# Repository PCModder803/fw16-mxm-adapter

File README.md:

# FW16 Expansion Bay -> MXM adapter : schematic v4 (full mock-up, with placeholders)

Open `fw16_mxm_adapter.kicad_pro` in KiCad (built and checked with KiCad 10). The project
footprint library `fw16_mxm.pretty` is registered through `fp-lib-table`.
`fw16_mxm_adapter_schematic.pdf` shows the same schematic (one A0 sheet) with no KiCad needed.
`fw16_mxm_adapter_bom_draft.csv` lists every part with its footprint and notes; "TBD" marks an unresolved choice.

Target: Graphics Module bay, MXM 3.0 Type B card (X-Vision RX 6600 XT): 100 W total board power
(105 W TDP), 82 x 105 mm, 0-55 C operating, supplied bare with no cooler. At 100 W it draws 5.0 A from
VSYS at 20 V (AC) or 6.6 A at 15.2 V (battery), within the eFuse's 9.9 A limit and the host's 10.5 A.

Third-party documents (Framework's PDFs and drawings, datasheets, and the crops in `reference/evidence/`)
are kept locally but not published in this repository; the tables below name each source.
The community board this started from is on the Framework forum (t/74018).

## What is in the schematic
| Block | Parts | Source |
|---|---|---|
| Signal interposer | J1, 74 pins | FrameworkComputer/ExpansionBay Electrical/README.md |
| Power interposer | J2, 74 pins | same |
| MXM 3.0 socket | J3, 278 pins (Foxconn AS0B826-S55B-7H) | MXM 3.1 r1.0 Table 3.2/3.3 (all 278 pins checked); ADLINK MXM-AXe + Advantech SKY-MXM-RTX3000 manuals |
| MXM system-board parts | U6 SN74LV1T08 (card PWR_EN = 1.8 V host PWR_EN AND eFuse PG, at 3.3 V; R19 100k pull-down, R40 PG pull-up, C48); R36 PEX_STD_SW# 7.15k pull-down; R37 PWR_GOOD and R38 TH_ALERT# 10k pull-ups | MXM 3.1 sec 3.4.1, Tables 3.6, 3.11, 3.30 |
| PCIe x8 | R20-R35 0R (host->card), C10-C25 220 nF (card->host) | community board + a-little-wifi frmw-16-MXM-E-port |
| DisplayPort A (internal panel) | C26-C35 100 nF DC blocking; HPD direct, R14 DNP | Advantech manual: DC blocking + HPD conditioning on the system board |
| Card power | D1 SMBJ20A; U1 TPS25982 eFuse: ILIM 147R = 9.9 A, UVLO 6.5 V (442k/100k), IMON 1.33k, dVdT 4.7 nF (~1 V/ms), retry 2.2 nF (~100 ms, 4 retries then latch-off); C1/C4 EEH-ZA1V101P | TI datasheet SLVSEI3D equations; SMBJ20A / EEH-ZA1V101P distributor data |
| 5 V / 3.3 V | host 5V_ALW (2.5 A) / 3V3_ALW (2.0 A), C2/C3 bulk | ExpansionBay README |
| Power control | host PWR_EN (1.8 V APU GPIO) -> U6 -> MXM PWR_EN; MXM PWR_GOOD -> host PWR_GOOD and pin 53 | MXM 3.1 sec 3.4.1; 1.8 V level from Framework forum t/74018 post 233; U6 per TI SCLS739F |
| PEX_RST# source | R41 0R (fitted): host PEX_RST#. R42 0R DNP: power pin 52 (EC's EXT_SSD1_RST# in SSD-mode descriptors). Fit one only | Fallback for the BIOS dropping PEX_RST# with x8 descriptors (forum t/74018 posts 201-203) |
| Thermal / panel | TH_OVERT#, TH_ALERT#, PNL_* straight J1 <-> J3 | community board, a-little-wifi |
| Module EEPROM | U3 BR24G32 (32 Kbit) at 0x50 on I2C_*_ALW | FW EC gpu_configuration.c reads 0x50 with 16-bit offsets |
| Module ID | R1/R2 330k on ID0/ID1 -> BOARD_VERSION_12 on both = "dual interposer device" | FW EC gpu.c + adc.c thresholds; forum t/74018 original poster: 330k always passed detection |
| Power pins 52/53 | R13 0R: PWR_GOOD -> pin 53 (FBVDD_PWRGD in GPU mode); pin 52 (GC6_FB_EN3V3) NC; MXM SMB_CLK/DAT NC | FW16 7040 mainboard interface schematic p.3 (UC77 / UC78) |
| Fans (graphics bay) | J4/J5 Hefeng AFC58-S04FIA-R1: 1 +12V, 2 SPEED, 3 PWM, 4 GND | FW_EXPANSION_BAY_PCB sheet 2 pin table; Hefeng AFC58 drawing; Cooler Master UMA fan spec (FPC 1 = -, 4 = +, mirrored) |
| Fan-control sensor | U4 F75303M (MSOP-10) @0x4D on I2C_*_ALW, remote diodes Q1/Q2 (MMBT3906) on the card's VRM / VRAM, C46/C47 2.2 nF across D+/D- | Framework PCIE_THERMAL_3RDPARTY descriptor; pinout, filter caps and address 0x4D (8-bit 0x9A) from the FW16 mainboard's own F75303M (7040 interface schematic p.9) |

## Footprints
- Stock KiCad footprints for passives, D1 (D_SMB), U3 (TSSOP-8) and U4 (MSOP-10_3x3mm_P0.5mm).
- U4 F75303M pinout: 1 VCC, 2 DP1, 3 DN1, 4 DP2, 5 DN2, 6 GND, 7 THERM#, 8 ALERT#, 9 SDA, 10 SCL, read
  from the FW16 mainboard's own sensor UTH1 (7040 interface schematic p.9).
- `TI_RGE0024M_VQFN-24_4x4mm_P0.5mm_2EP` (U1): TI example board layout 4223975/B. Pads 0.575 x 0.24 at
  0.5 mm, rows at 3.825 mm; pad 25 (IN) 2.7 x 1.45 at y -0.625, pad 26 (GND) 2.7 x 0.85 at y +0.925.
  Paste is not windowed yet; use TI's stencil drawing.
- `Hefeng_AFC58-S04F_1x04_P0.5mm_Horizontal` (J4/J5): Hefeng drawing. Pads 0.30 x 1.10 at 0.5 mm; nail pads
  1.0 x 2.0, inner edge 1.60 from pin 1, top edge 1.60 below the signal pads (read off the drawing; check it).
- Crops of the source drawings for both, and for the fan pinout, are kept locally in `reference/evidence/`
  (not published here).
- The interposer and MXM footprints in `fw16_mxm.pretty` were built from the community board in `reference/`:
  - `FW16_FXBeam_Signal` / `FW16_FXBeam_Power`: the community interposer footprint split in two, with pads
    renumbered by position to the Framework README pin numbers. This also removes the duplicate PJ1/PJ2/PJ3
    pad bug. Both footprints keep the original origin, so **J1 and J2 must be placed at the same XY**.
    The pad geometry is unverified against the FXBeam drawing.
  - `MXM3_AS0B826-S55B-7H`: the merged power pads are split so every MXM pin has a pad.
    S55B is chosen: 5.5 mm overall with a 2.7 mm gap under the card (Critical Link wiki; Foxconn's sheet
    gives only the overall height). The adapter PCB is 1.2 mm, matching Framework's reference board and its
    M2 inserts. Checked against Foxconn's AS-series datasheet: all pad positions match; pegs set to its
    1.10 / 1.60 mm; courtyard added.
  - The 2.7 mm interposer screw holes are 16.65 mm apart, matching Framework's FW_EXPANSION_BAY_PCB_0807
    drawing (`reference/framework_pcb_ref/`). They still need a solder ring for the ES00000NY00 insert.
- Every symbol pin has a matching footprint pad (checked from the netlist); all 88 parts have footprints.

## How the FW16 EC handles the bay (from FrameworkComputer/EmbeddedController, lotus sources)
- The EC reads ID0/ID1 on its ADC. BOARD_VERSION_12 on both is "dual interposer device". The bay only
  powers up while the F_BEAM hatch switch is closed.
- It then turns on the module's 3V/5V and waits 150 ms. Next it reads the EEPROM at 0x50 (fallback 0x52)
  with 16-bit offsets on I2C_PORT_GPU0, the ALW bus.
- **VSYS and the fans are enabled only by the EEPROM descriptor.** A blank EEPROM makes the EC fall back
  to dual-SSD mode (PCIe x4x2) with no GPU power.
- Program the descriptor from ExpansionBayConfigurationGenerator `PCIE_THERMAL_3RDPARTY`. That gives
  PCIE_8X1, VSYS_EN, FAN_EN, 3V_5V_EN and an F75303 at 0x4D for fan control. Two changes:
  - `GPU_PCIE_MUX_SEL` to LOW: the template sets it HIGH, which reroutes DP_A AUX to the SSD2 PCIe clock.
  - `gpio2` (GPU_2A2_GPIO2_EC) to `GPIO_FUNC_ACDC`, `GPIO_OUTPUT_LOW`, `POWER_S3`, as in Framework's r23m
    descriptor. The EC then drives it with `extpower_is_present()` (high on any external power), which
    sets the card's PWR_LEVEL through U2. Left as the template's input, the card stays at reduced power.
- The EC sets `GPU_PRESENT`, which the internal-panel eDP mux path uses, only for vendor `GPU_AMD_R23M`.
  Driving the laptop's own screen from the MXM card may need firmware changes.
- Power pins 52/53 are `GPU_1F3_MUX1` / `GPU_1G3_MUX2` in the EC ("cannot be controlled directly"):
  they go through mainboard switch UC77. With GPU_PCIE_MUX_SEL low they carry GC6_FB_EN3V3 (out) and
  FBVDD_PWRGD (in), and the mainboard ANDs FBVDD_PWRGD with DGPU_PWROK into ALL_GPWRGD (7040 interface
  schematic p.3). The adapter drives pin 53 from PWR_GOOD through R13.
- On Framework's own AMD module, GPIO0_EC is the temperature-fault input, GPIO1_EC is HPD from its PD
  controller, and GPIO2_EC is the AC/DC-mode output. GPIO3_EC is unused.

## Placeholders still in the design (TBD)
- U4 F75303M ALERT#/THERM# are open-drain and left unconnected; they need pull-ups only if something
  reads them.
- R14 (DNP): not needed. MXM 3.1 puts the 100k DP_A_HPD pull-down on the module.
- Unconnected by choice: TH_PWM, GPIO0/1/3_EC, DGPU_PWM_SEL, WAKE#, MXM SMB_CLK/DAT, power pins 52/54.
- Cover: the stock cover is too low over the card. It needs a 3D-printed replacement whose inside is flat
  at the 15.3 mm level. With S55B on 1.2 mm that leaves ~5 mm over the inductors and ~8.4 mm over the die
  for the cooler. See `RESEARCH_TODO.md` item 6.
- PWR_LEVEL: U2 (74LVC1G07) pulls the card's PWR_LEVEL low whenever GPIO2_EC is low, i.e. on battery.
  The card must then cut power by at least 20% (MXM 3.1 sec 3.4.14); how much the X-Vision VBIOS actually
  cuts is unknown. Leave U2 unfitted for always-full power.

## What was verified (kicad-cli 10)
- ERC: only "symbol library not in library table" warnings, for the symbols embedded by the generator.
  Connector pins are typed passive, so ERC can't catch direction mistakes.
- Netlist: every PCIe/DP lane, sideband net, power rail, eFuse pin and fan net was checked against the
  intended pins.
- Not verified: the schematic drawing's layout in detail (the PDF has only been looked over as a whole),
  and anything electrical or physical on hardware.

## Evidence for the PCIe direction
MXM lane names are system-relative: host PEX_TX -> MXM PEX_TX, MXM PEX_RX -> host PEX_RX.
Sources: a-little-wifi's frmw-16-MXM-E-port and mxm-immobilizer, the community board, and XPModder's IO
module for the Framework side. Confirmed by MXM 3.1 Table 3.6, and on the Framework side by the 7040
interface schematic: host->module lanes are PEG_CTX_C_GRX_* (already AC-coupled on the mainboard), so
R20-R35 stay 0R and the adapter's C10-C25 couple the card's TX.

## PCB: mechanical placement draft (not for fab)
`fw16_mxm_adapter.kicad_pcb` is generated by `generate_pcb.py` (run it with KiCad's Python, which has the
`pcbnew` module). `fw16_mxm_adapter_pcb_draft.pdf` shows it without KiCad. It is a fit study, laid out for
the printed bottom frame below. The positions and the outline live in `layout.py`, which the frame
generator uses too:
- Outline: Framework's RX 7700S module board (from `reference/fw_7700s_board_outline.csv`), extended on the
  left, at the rear (to the printed frame's rear wall, which sits 3.7 mm further back) and at the front-left for the MXM socket. 1.2 mm, 6
  copper layers as a placeholder for a JLCPCB stackup.
- Placed: J1/J2 interposers at the 7700S position, J3 along the left edge with the card extending across the
  bay, J4/J5 fan connectors near the 7700S positions, a screw hole and a rear insert at the 7700S fixings.
  Everything else sits unplaced beside the board, with nets, so the ratsnest shows. No tracks.
- Card size: laid out for a Type B card (82 x 105). A Type A card (82 x 70) fits the same socket and the
  same two hold-downs (H3/H4, 66 mm from the finger edge, which is also where Type B cards have their side
  holes), so one board takes either; its far edge is marked on the drawing. Type A cards are limited to
  about 55-60 W.
- User layers: the MXM card outline, the interposer stiffener keep-out (4.45 mm tall; the card must not
  overlap it), and the printed frame's inner walls and cover bosses.
- Why a new frame: in the stock shell the socket's rear end overruns the rear wall (the card is pinned
  behind the interposer stiffener), and card plus socket need ~109.7 mm across where the cover-screw
  bosses leave 107.05 mm (`RESEARCH_TODO.md` item 7b).

## Printed bottom frame (mockup)
`generate_frame.py` takes Framework's bottom frame out of their graphics-module STEP and changes the
inside for this adapter:
- lengthened by 3.7 mm at the rear over the full width, so the socket's rear end fits and there is
  room behind the card for heat pipes;
- the cover-screw bosses moved outboard;
- a few small features removed.

It checks the result against the board, socket and card, and writes `mechanical/printed_frame_mockup.step`
and `.stl`, with renders in `mechanical/preview/`. It is not for print yet: `FRAME_PLAN.md` has the
changes, the fit check and what to check first (the laptop's clearance behind the longer rear, among others).
The frame files are CC BY 4.0, credited to Framework Computer (`mechanical/README.md`).

## Still to do
`RESEARCH_TODO.md` lists everything that needs a document, a measurement or a laptop. After that: write
the EEPROM descriptor, then PCB layout.

`generate_schematic.py` regenerates the schematic (python3 generate_schematic.py out.kicad_sch);
edit it, or have Claude Code edit it, instead of hand-editing the .kicad_sch.

## License
Copyright PCModder803 2026.

This source describes Open Hardware and is licensed under the CERN-OHL-S v2 (see `LICENSE`).
You may redistribute and modify this source and make products using it under the terms of the
CERN-OHL-S v2 (https://ohwr.org/cern_ohl_s_v2.txt). This source is distributed WITHOUT ANY EXPRESS OR
IMPLIED WARRANTY, INCLUDING OF MERCHANTABILITY, SATISFACTORY QUALITY AND FITNESS FOR A PARTICULAR
PURPOSE. Please see the CERN-OHL-S v2 for applicable conditions.

Exceptions: `mechanical/` holds a modified version of Framework Computer's bottom frame and is licensed
CC BY 4.0 (see `mechanical/README.md`). `reference/fw_7700s_board_outline.csv` is also derived from
Framework's CC BY 4.0 model and credits it in its header.

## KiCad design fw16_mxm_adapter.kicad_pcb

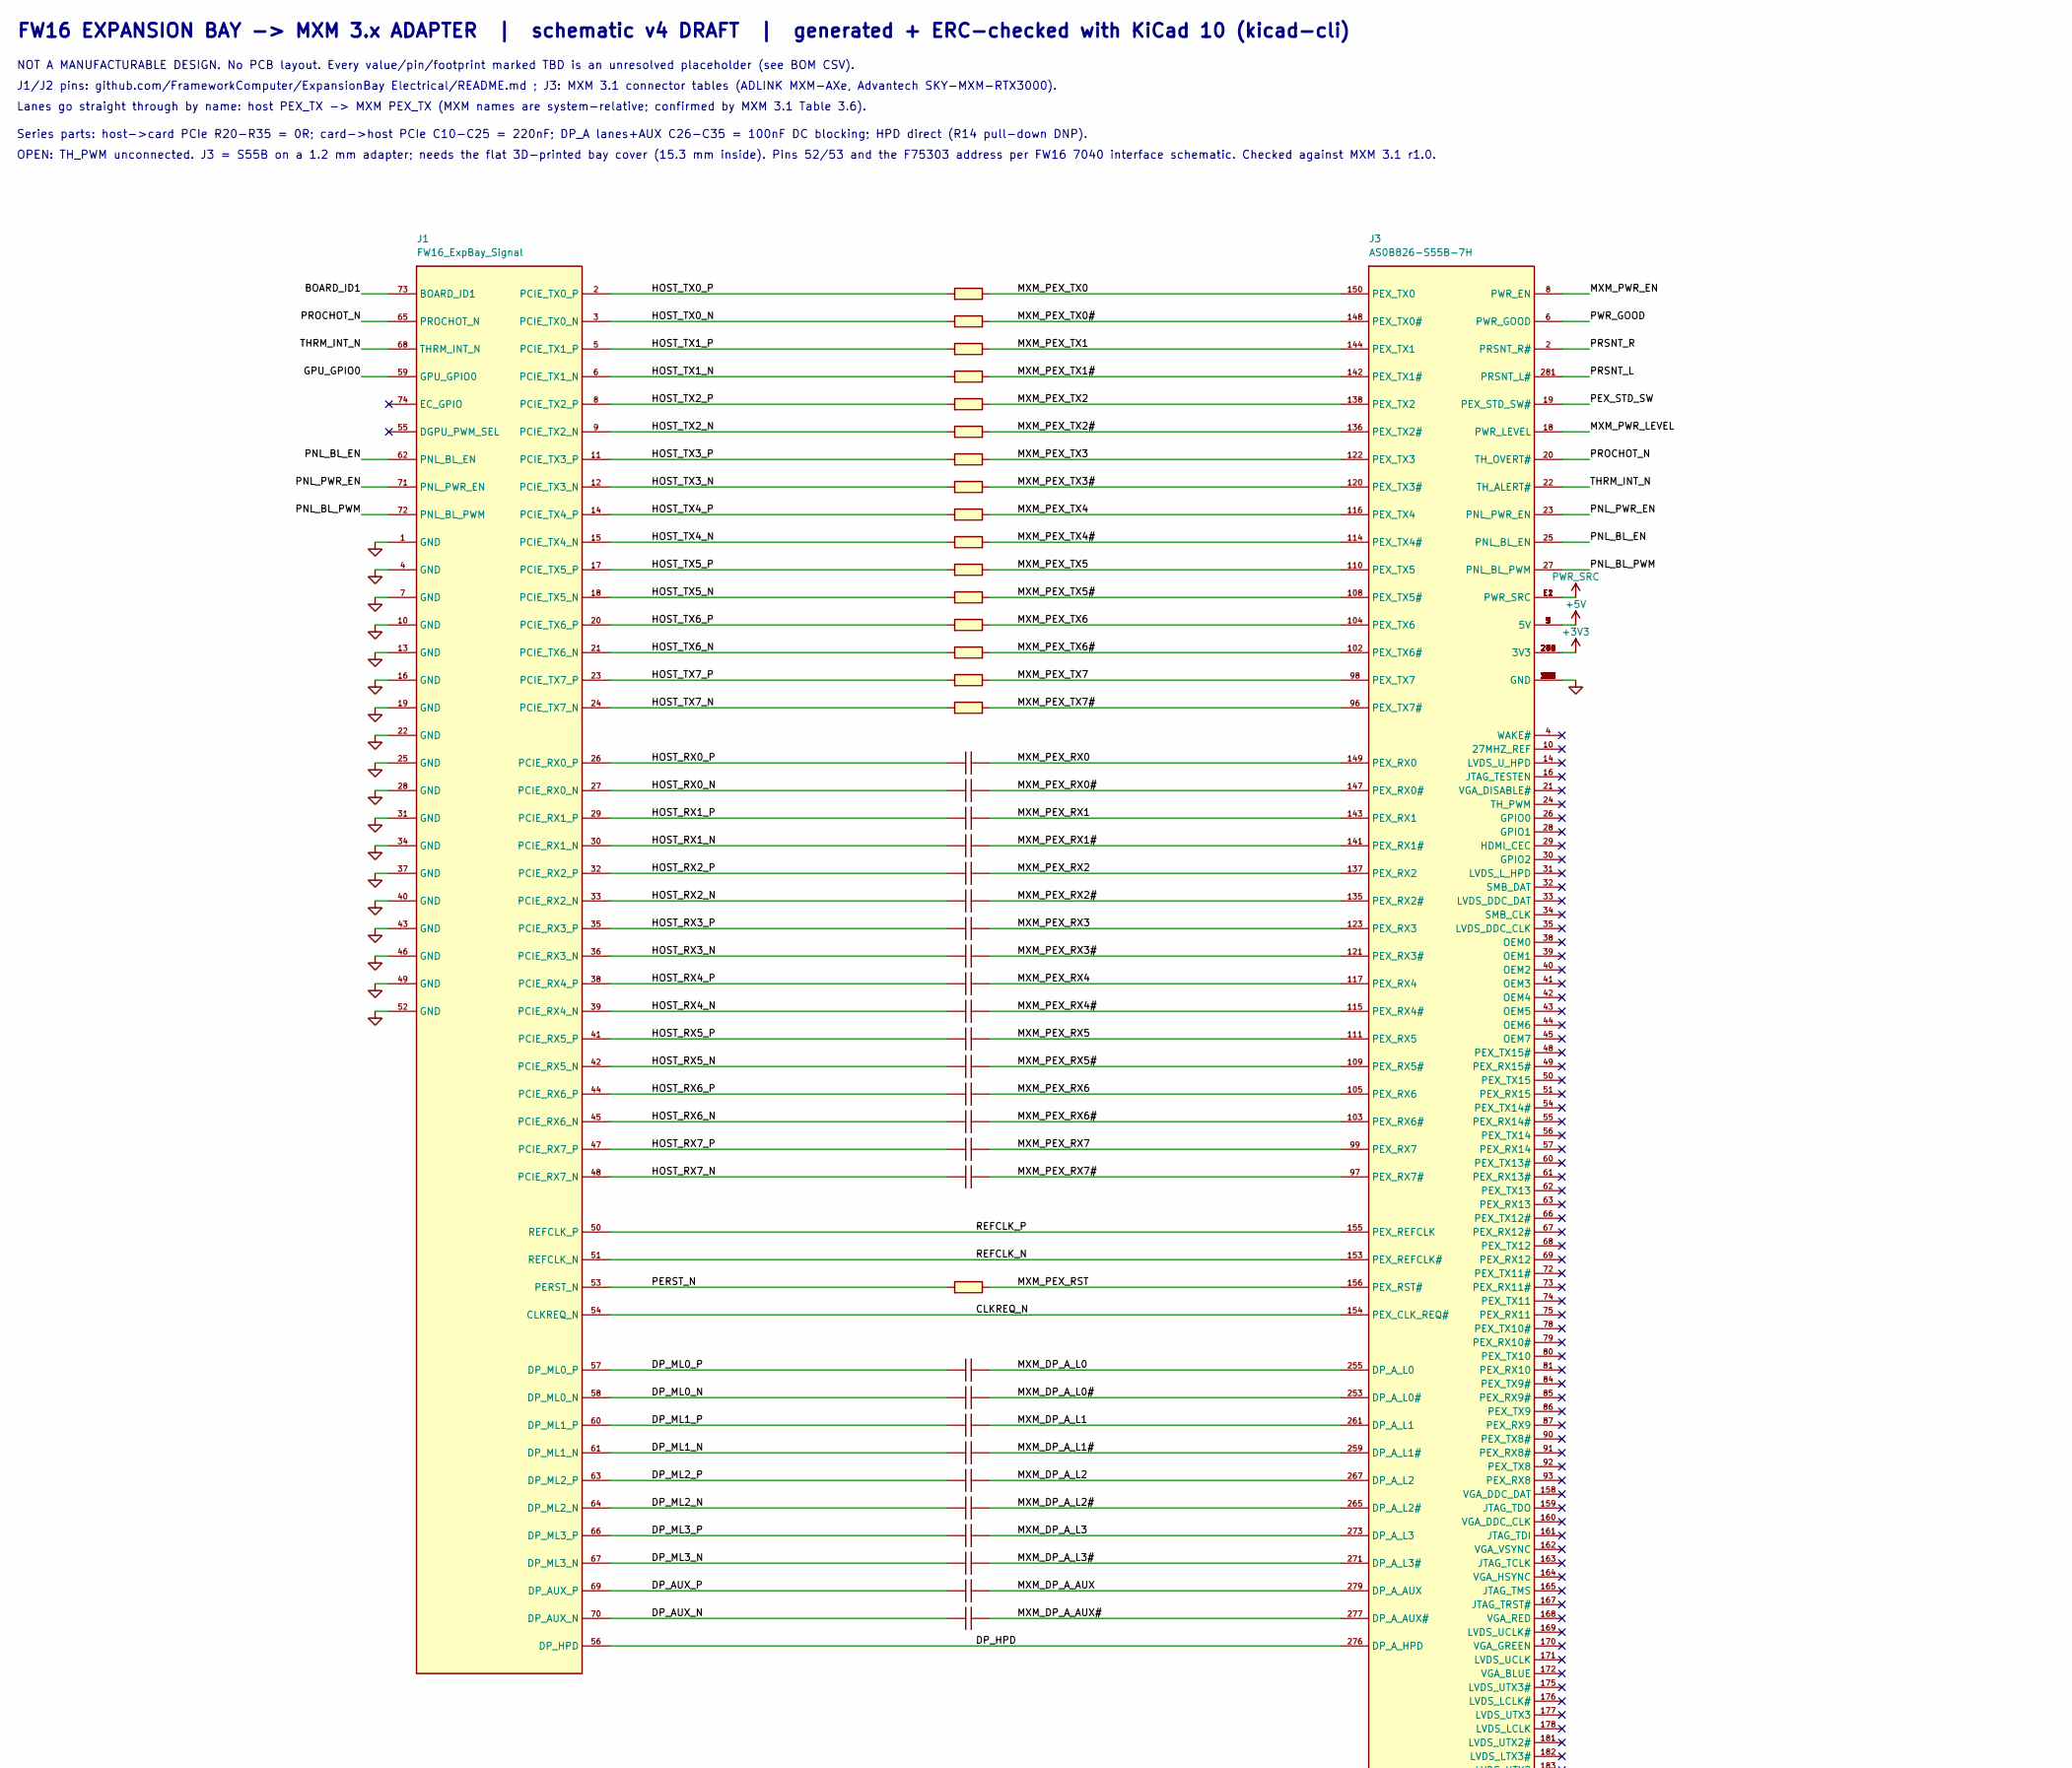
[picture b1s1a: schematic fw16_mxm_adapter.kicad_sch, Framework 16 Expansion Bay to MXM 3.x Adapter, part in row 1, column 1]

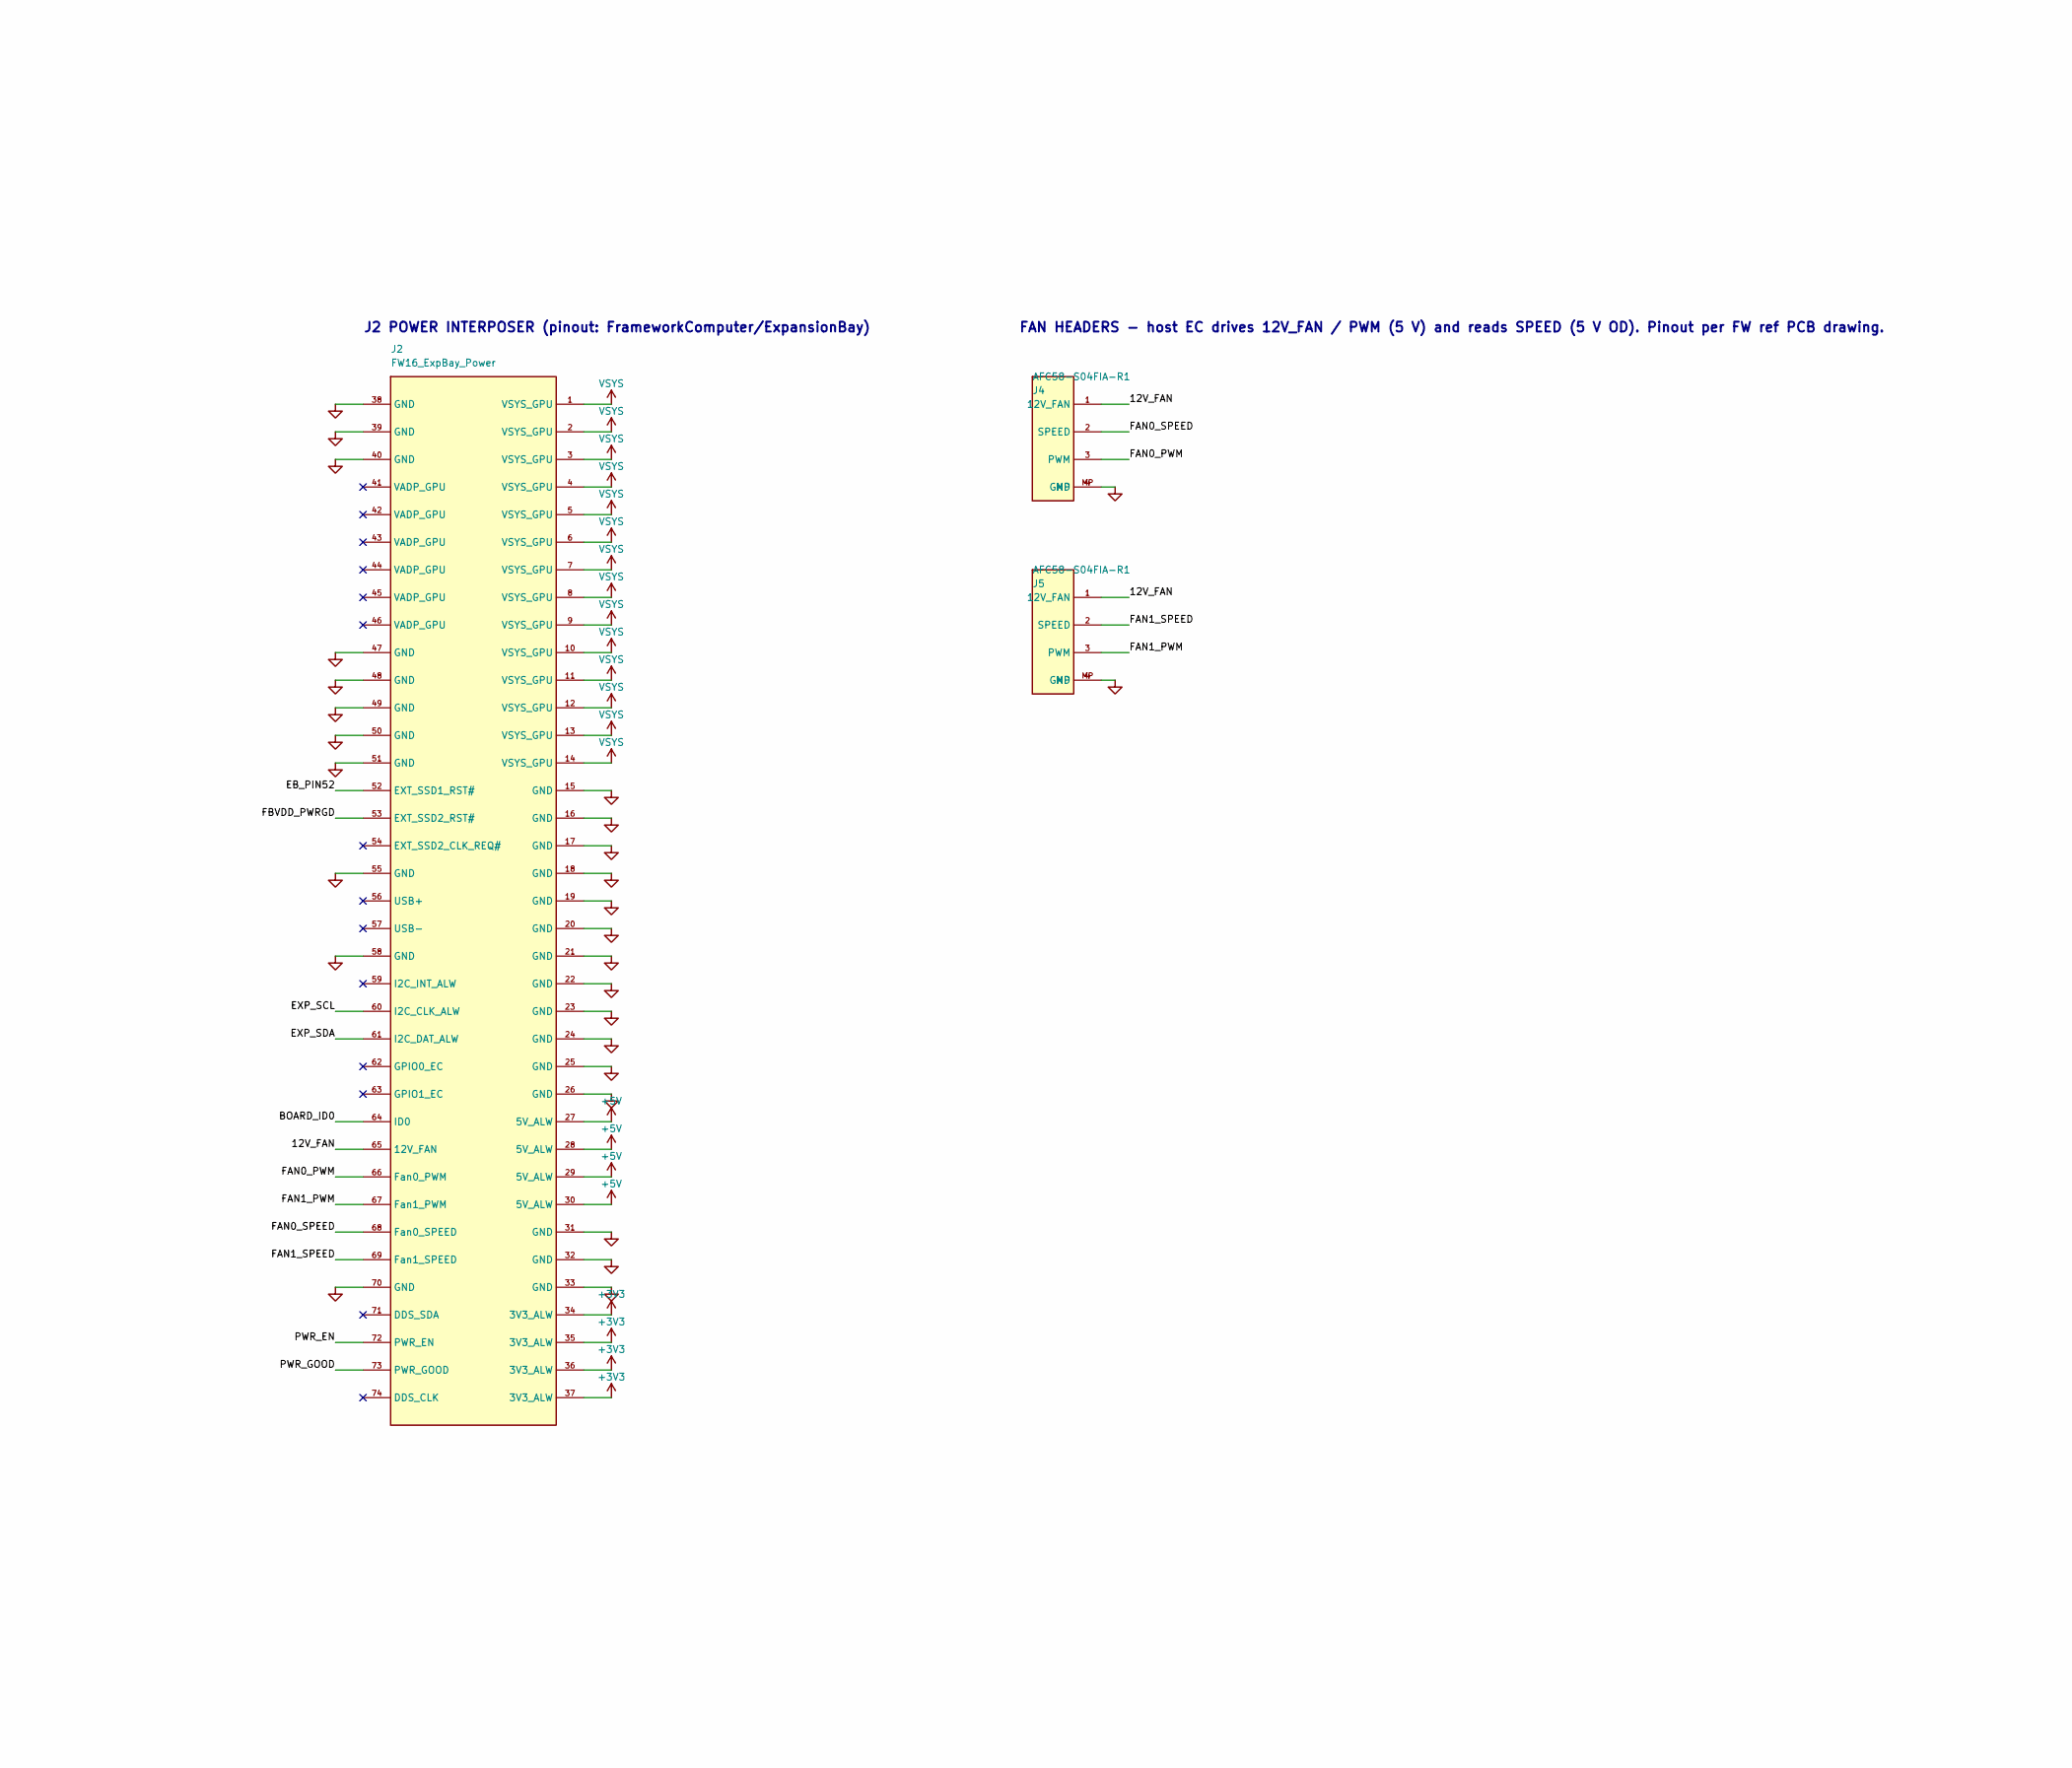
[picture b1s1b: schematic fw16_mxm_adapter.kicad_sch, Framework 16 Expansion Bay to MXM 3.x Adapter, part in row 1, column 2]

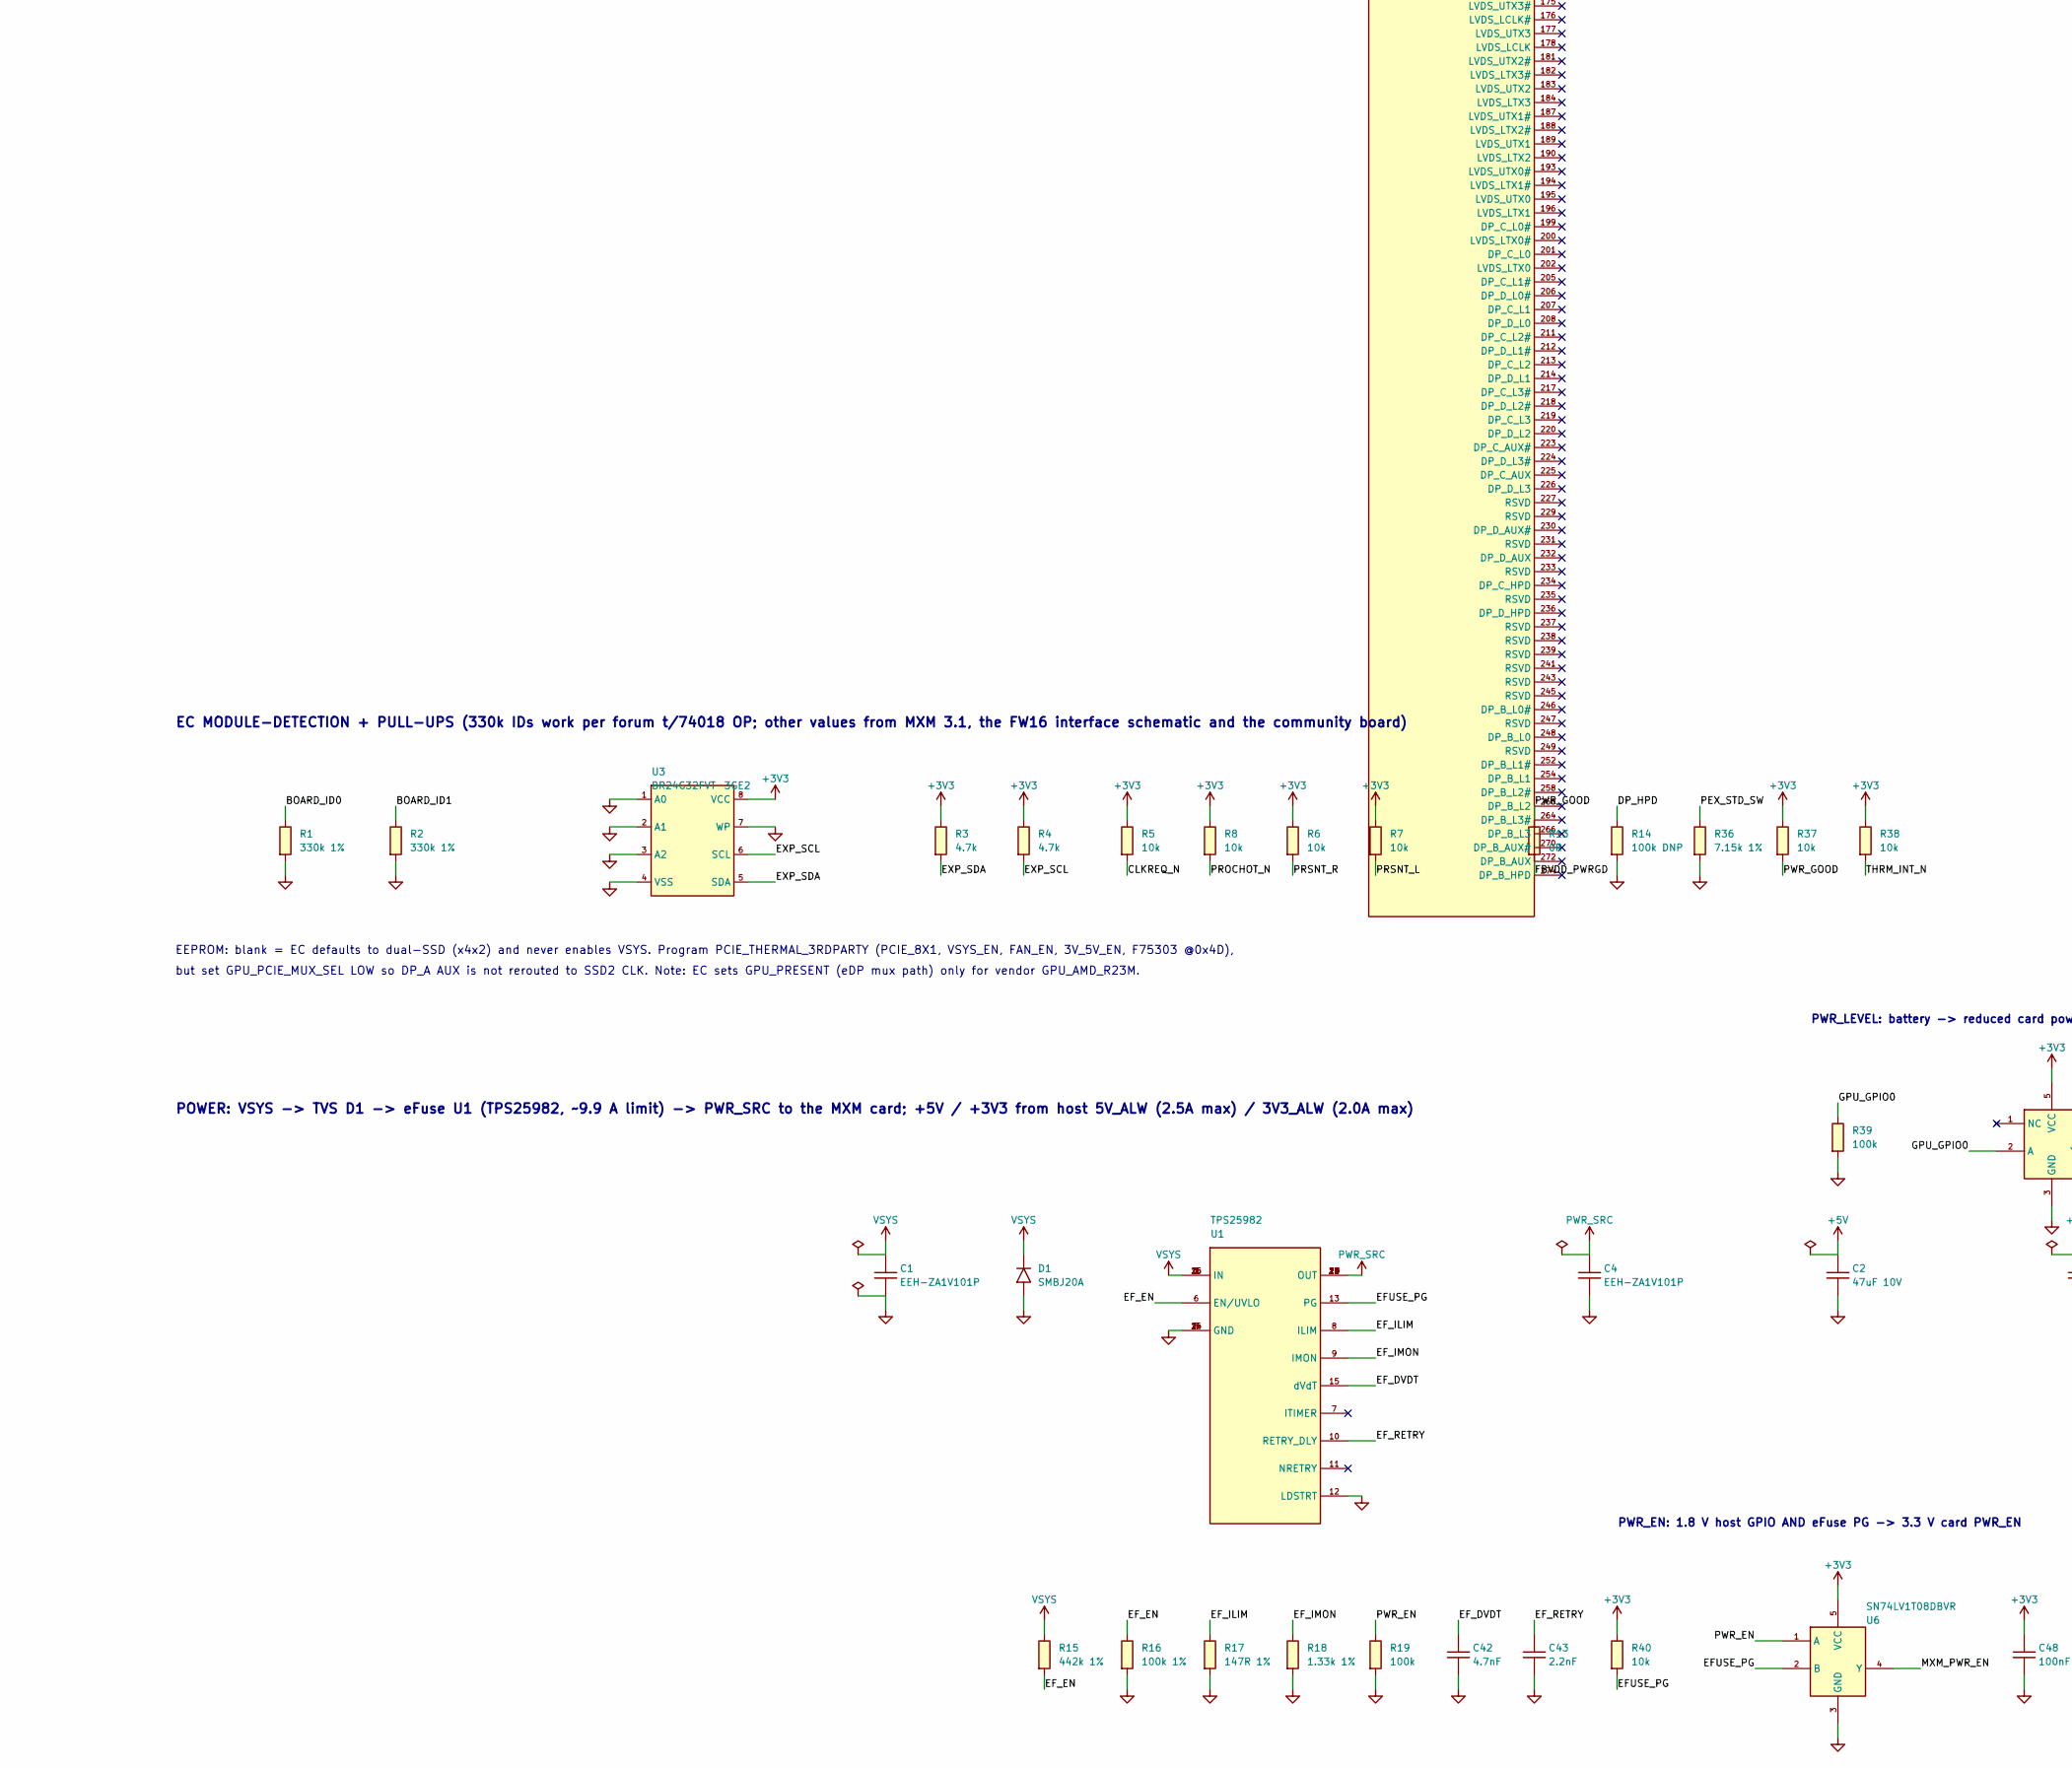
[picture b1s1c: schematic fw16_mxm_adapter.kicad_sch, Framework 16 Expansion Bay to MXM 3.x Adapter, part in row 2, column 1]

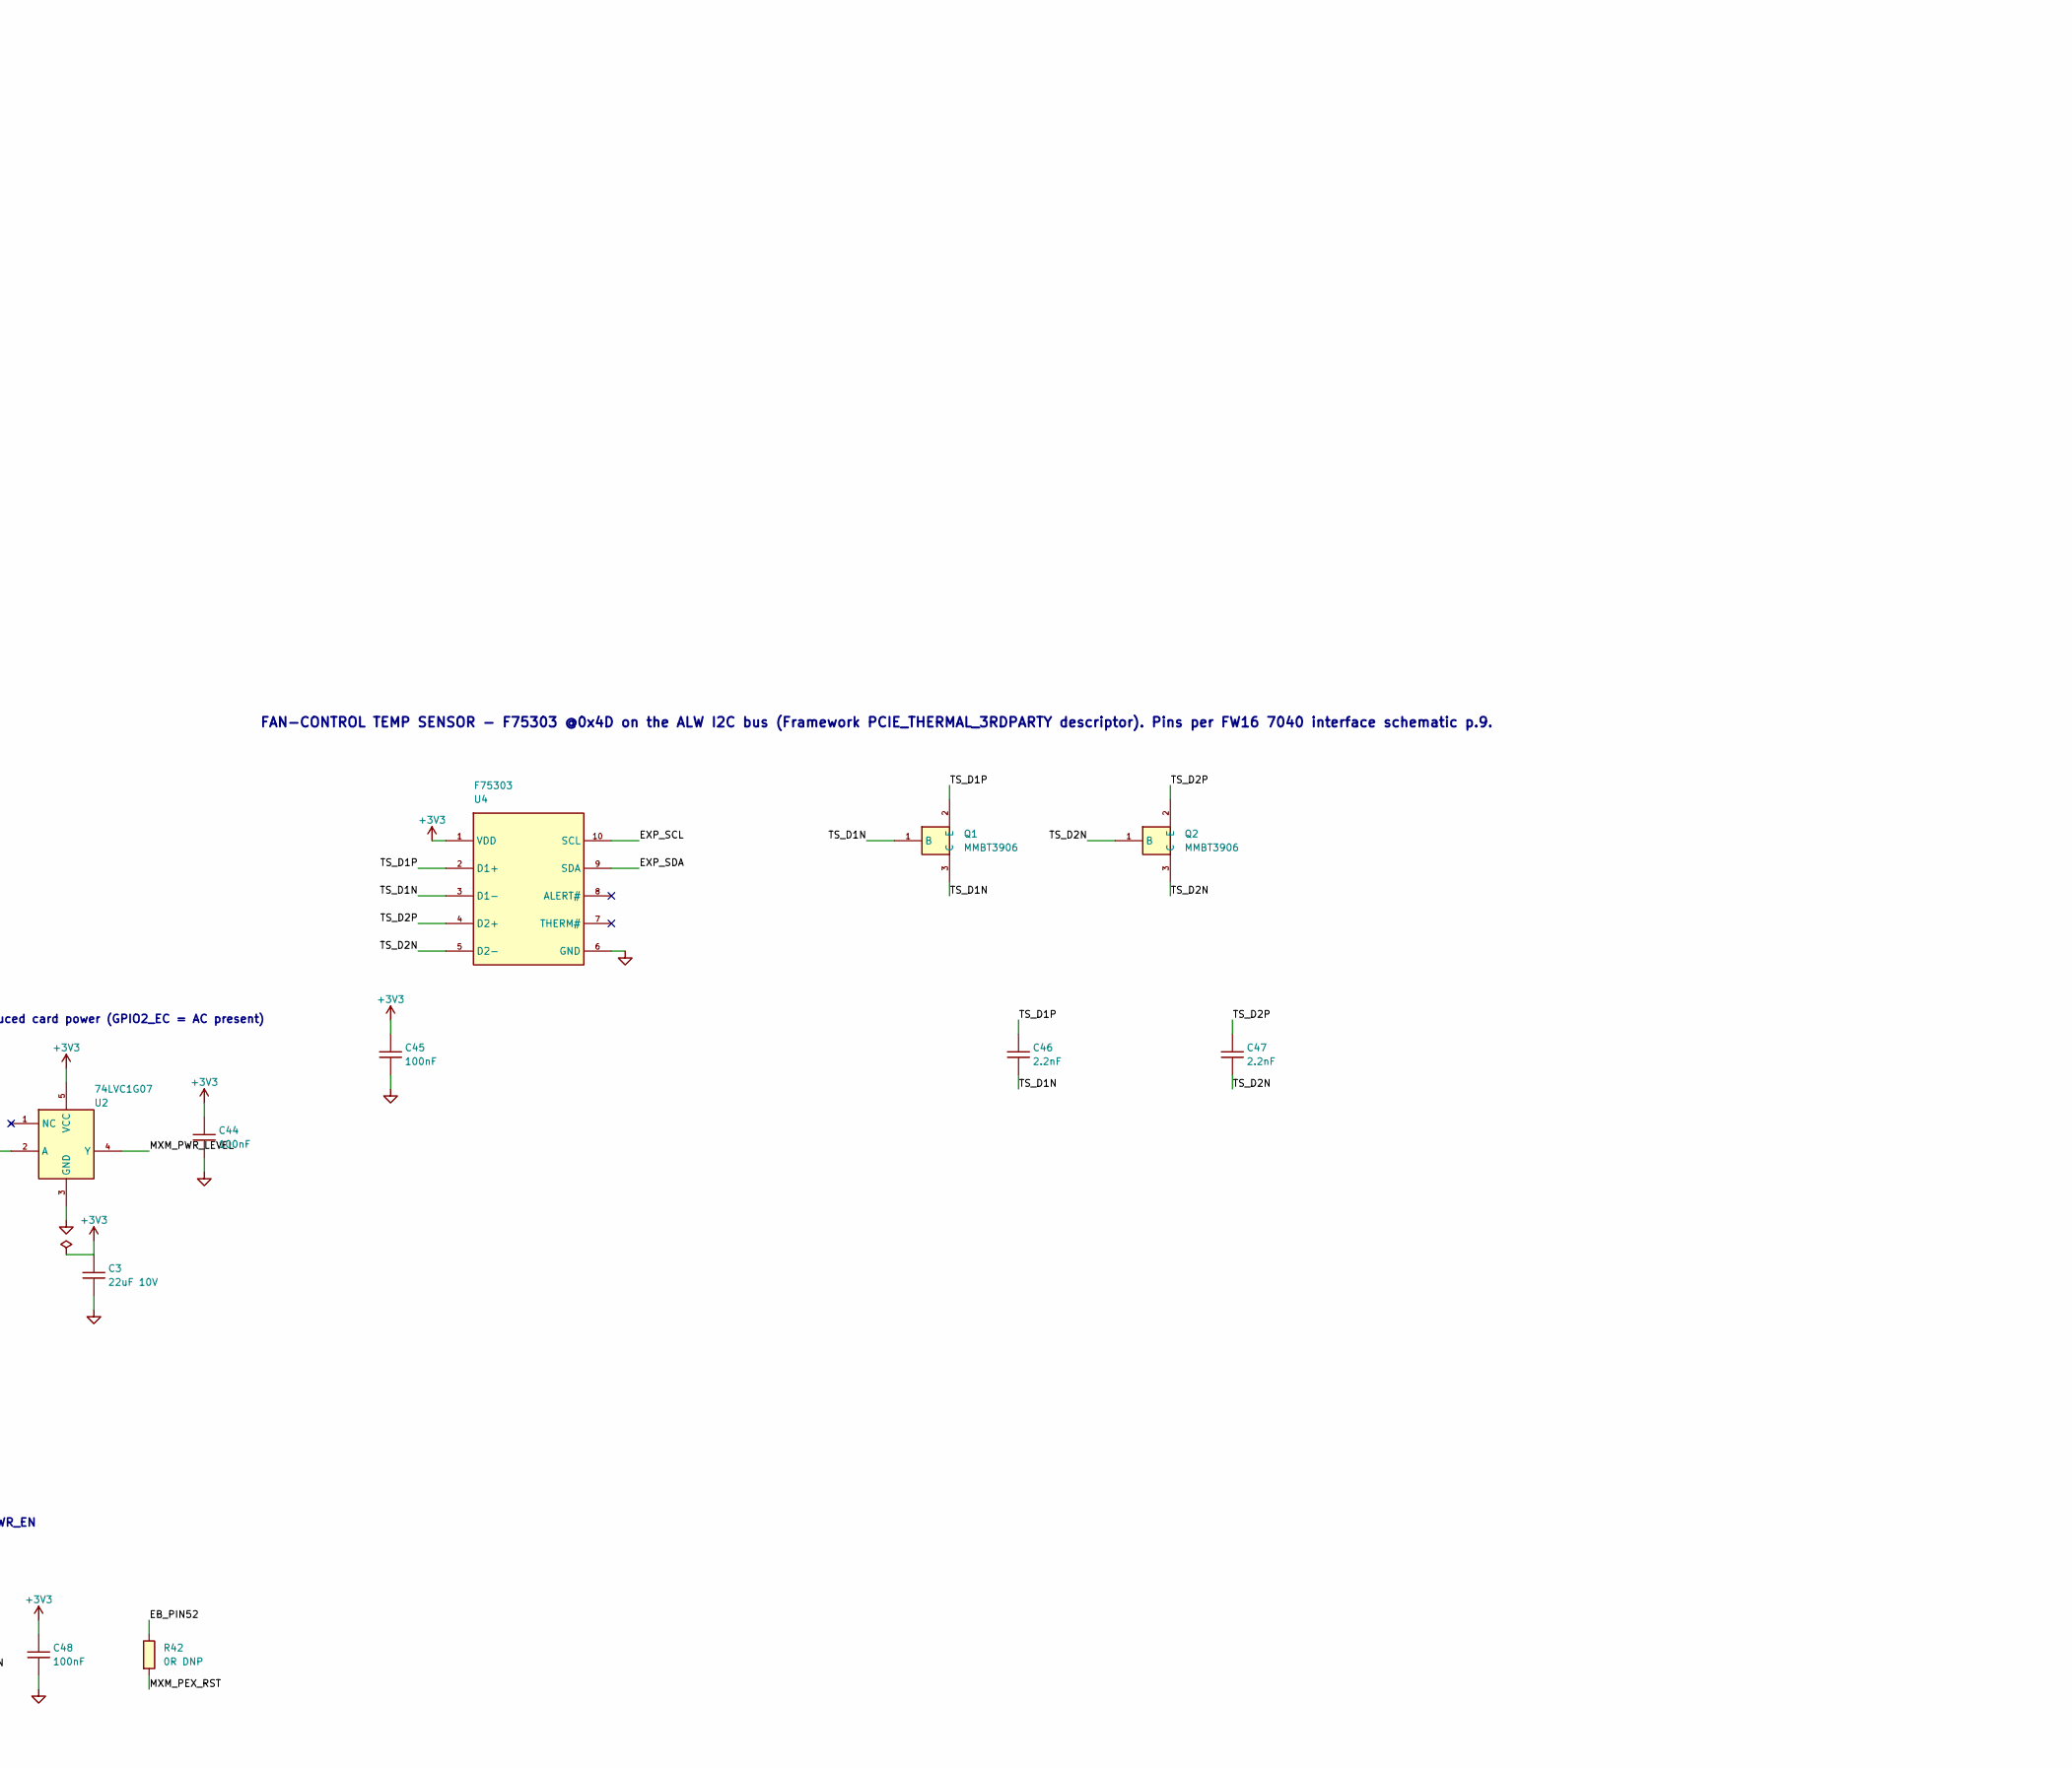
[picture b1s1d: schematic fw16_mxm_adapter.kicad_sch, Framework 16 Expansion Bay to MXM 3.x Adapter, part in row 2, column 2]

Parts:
C1, C4: EEH-ZA1V101P; CP_Elec_8x10.5
C2: 47uF 10V; C_1206_3216Metric
C3: 22uF 10V; C_1206_3216Metric
C10, C11, C12, C13, C14, C15, C16, C17, C18, C19, C20, C21, C22, C23, C24, C25: 220nF; C_0402_1005Metric
C26, C27, C28, C29, C30, C31, C32, C33, C34, C35, C44, C45, C48: 100nF; C_0402_1005Metric
C42: 4.7nF; C_0603_1608Metric
C43: 2.2nF; C_0603_1608Metric
C46, C47: 2.2nF; C_0402_1005Metric
D1: SMBJ20A; D_SMB
J1: FW16_ExpBay_Signal; FW16_FXBeam_Signal
J2: FW16_ExpBay_Power; FW16_FXBeam_Power
J3: AS0B826-S55B-7H; MXM3_AS0B826-S55B-7H
J4, J5: AFC58-S04FIA-R1; Hefeng_AFC58-S04F_1x04_P0.5mm_Horizontal
Q1, Q2: MMBT3906; SOT-23
R1, R2: 330k 1%; R_0603_1608Metric
R3, R4: 4.7k; R_0603_1608Metric
R5, R6, R7, R8, R37, R38, R40: 10k; R_0603_1608Metric
R13: 0R; R_0603_1608Metric
R14: 100k DNP; R_0603_1608Metric
R15: 442k 1%; R_0603_1608Metric
R16: 100k 1%; R_0603_1608Metric
R17: 147R 1%; R_0603_1608Metric
R18: 1.33k 1%; R_0603_1608Metric
R19, R39: 100k; R_0603_1608Metric
R20, R21, R22, R23, R24, R25, R26, R27, R28, R29, R30, R31, R32, R33, R34, R35, R41: 0R; R_0402_1005Metric
R36: 7.15k 1%; R_0603_1608Metric
R42: 0R DNP; R_0603_1608Metric
U1: TPS25982; TI_RGE0024M_VQFN-24_4x4mm_P0.5mm_2EP
U2: 74LVC1G07; SOT-23-5
U3: BR24G32FVT-3GE2; TSSOP-8_4.4x3mm_P0.65mm
U4: F75303; MSOP-10_3x3mm_P0.5mm
U6: SN74LV1T08DBVR; SOT-23-5

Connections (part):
+3V3: C3.1, C44.1, C45.1, C48.1, J2.34 (3V3_ALW), J2.35 (3V3_ALW), J2.36 (3V3_ALW), J2.37 (3V3_ALW), J3.240 (3V3), J3.242 (3V3), J3.278 (3V3), J3.280 (3V3), R3.1, R4.1, R5.1, R6.1, R7.1, R8.1, R37.1, R38.1, R40.1, U2.5 (VCC), U3.8 (VCC), U4.1 (VDD), U6.5 (VCC)
+5V: C2.1, J2.27 (5V_ALW), J2.28 (5V_ALW), J2.29 (5V_ALW), J2.30 (5V_ALW), J3.1 (5V), J3.3 (5V), J3.5 (5V), J3.7 (5V), J3.9 (5V)
/12V_FAN: J2.65 (12V_FAN), J4.1 (12V_FAN), J5.1 (12V_FAN)
/BOARD_ID0: J2.64 (ID0), R1.1
/BOARD_ID1: J1.73 (BOARD_ID1), R2.1
/CLKREQ_N: J1.54 (CLKREQ_N), J3.154 (PEX_CLK_REQ#), R5.2
/DP_AUX_N: C35.1, J1.70 (DP_AUX_N)
/DP_AUX_P: C34.1, J1.69 (DP_AUX_P)
/DP_HPD: J1.56 (DP_HPD), J3.276 (DP_A_HPD), R14.1
/DP_ML0_N: C27.1, J1.58 (DP_ML0_N)
/DP_ML0_P: C26.1, J1.57 (DP_ML0_P)
/DP_ML1_N: C29.1, J1.61 (DP_ML1_N)
/DP_ML1_P: C28.1, J1.60 (DP_ML1_P)
/DP_ML2_N: C31.1, J1.64 (DP_ML2_N)
/DP_ML2_P: C30.1, J1.63 (DP_ML2_P)
/DP_ML3_N: C33.1, J1.67 (DP_ML3_N)
/DP_ML3_P: C32.1, J1.66 (DP_ML3_P)
/EB_PIN52: J2.52 (EXT_SSD1_RST#), R42.1
/EFUSE_PG: R40.2, U1.13 (PG), U6.2 (B)
/EF_DVDT: C42.1, U1.15 (dVdT)
/EF_EN: R15.2, R16.1, U1.6 (EN/UVLO)
/EF_ILIM: R17.1, U1.8 (ILIM)
/EF_IMON: R18.1, U1.9 (IMON)
/EF_RETRY: C43.1, U1.10 (RETRY_DLY)
/EXP_SCL: J2.60 (I2C_CLK_ALW), R4.2, U3.6 (SCL), U4.10 (SCL)
/EXP_SDA: J2.61 (I2C_DAT_ALW), R3.2, U3.5 (SDA), U4.9 (SDA)
/FAN0_PWM: J2.66 (Fan0_PWM), J4.3 (PWM)
/FAN0_SPEED: J2.68 (Fan0_SPEED), J4.2 (SPEED)
/FAN1_PWM: J2.67 (Fan1_PWM), J5.3 (PWM)
/FAN1_SPEED: J2.69 (Fan1_SPEED), J5.2 (SPEED)
/FBVDD_PWRGD: J2.53 (EXT_SSD2_RST#), R13.2
/GPU_GPIO0: J1.59 (GPU_GPIO0), R39.1, U2.2 (A)
/HOST_RX0_N: C11.1, J1.27 (PCIE_RX0_N)
/HOST_RX0_P: C10.1, J1.26 (PCIE_RX0_P)
/HOST_RX1_N: C13.1, J1.30 (PCIE_RX1_N)
/HOST_RX1_P: C12.1, J1.29 (PCIE_RX1_P)
/HOST_RX2_N: C15.1, J1.33 (PCIE_RX2_N)
/HOST_RX2_P: C14.1, J1.32 (PCIE_RX2_P)
/HOST_RX3_N: C17.1, J1.36 (PCIE_RX3_N)
/HOST_RX3_P: C16.1, J1.35 (PCIE_RX3_P)
/HOST_RX4_N: C19.1, J1.39 (PCIE_RX4_N)
/HOST_RX4_P: C18.1, J1.38 (PCIE_RX4_P)
/HOST_RX5_N: C21.1, J1.42 (PCIE_RX5_N)
/HOST_RX5_P: C20.1, J1.41 (PCIE_RX5_P)
/HOST_RX6_N: C23.1, J1.45 (PCIE_RX6_N)
/HOST_RX6_P: C22.1, J1.44 (PCIE_RX6_P)
/HOST_RX7_N: C25.1, J1.48 (PCIE_RX7_N)
/HOST_RX7_P: C24.1, J1.47 (PCIE_RX7_P)
/HOST_TX0_N: J1.3 (PCIE_TX0_N), R21.1
/HOST_TX0_P: J1.2 (PCIE_TX0_P), R20.1
/HOST_TX1_N: J1.6 (PCIE_TX1_N), R23.1
/HOST_TX1_P: J1.5 (PCIE_TX1_P), R22.1
/HOST_TX2_N: J1.9 (PCIE_TX2_N), R25.1
/HOST_TX2_P: J1.8 (PCIE_TX2_P), R24.1
/HOST_TX3_N: J1.12 (PCIE_TX3_N), R27.1
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
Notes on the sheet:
EC MODULE-DETECTION + PULL-UPS (330k IDs work per forum t/74018 OP; other values from MXM 3.1, the FW16 interface schematic and the community board)
PWR_LEVEL: battery -> reduced card power (GPIO2_EC = AC present)
EEPROM: blank = EC defaults to dual-SSD (x4x2) and never enables VSYS. Program PCIE_THERMAL_3RDPARTY (PCIE_8X1, VSYS_EN, FAN_EN, 3V_5V_EN, F75303 @0x4D),
but set GPU_PCIE_MUX_SEL LOW so DP_A AUX is not rerouted to SSD2 CLK. Note: EC sets GPU_PRESENT (eDP mux path) only for vendor GPU_AMD_R23M.
POWER: VSYS -> TVS D1 -> eFuse U1 (TPS25982, ~9.9 A limit) -> PWR_SRC to the MXM card; +5V / +3V3 from host 5V_ALW (2.5A max) / 3V3_ALW (2.0A max)
J2 POWER INTERPOSER (pinout: FrameworkComputer/ExpansionBay)
PWR_EN: 1.8 V host GPIO AND eFuse PG -> 3.3 V card PWR_EN
FAN HEADERS - host EC drives 12V_FAN / PWM (5 V) and reads SPEED (5 V OD). Pinout per FW ref PCB drawing.
FAN-CONTROL TEMP SENSOR - F75303 @0x4D on the ALW I2C bus (Framework PCIE_THERMAL_3RDPARTY descriptor). Pins per FW16 7040 interface schematic p.9.
FW16 EXPANSION BAY -> MXM 3.x ADAPTER | schematic v4 DRAFT | generated + ERC-checked with KiCad 10 (kicad-cli)
NOT A MANUFACTURABLE DESIGN. No PCB layout. Every value/pin/footprint marked TBD is an unresolved placeholder (see BOM CSV).
J1/J2 pins: github.com/FrameworkComputer/ExpansionBay Electrical/README.md ; J3: MXM 3.1 connector tables (ADLINK MXM-AXe, Advantech SKY-MXM-RTX3000).
Lanes go straight through by name: host PEX_TX -> MXM PEX_TX (MXM names are system-relative; confirmed by MXM 3.1 Table 3.6).
Series parts: host->card PCIe R20-R35 = 0R; card->host PCIe C10-C25 = 220nF; DP_A lanes+AUX C26-C35 = 100nF DC blocking; HPD direct (R14 pull-down DNP).
OPEN: TH_PWM unconnected. J3 = S55B on a 1.2 mm adapter; needs the flat 3D-printed bay cover (15.3 mm inside). Pins 52/53 and the F75303 address per FW16 7040 interface schematic. Checked against MXM 3.1 r1.0.

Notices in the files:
fw16_mxm_adapter.kicad_pcb:
Outline from Framework's RX 7700S module board (FW_GRAPHICS_MODULE_REF_00-1.stp, CC BY 4.0)
